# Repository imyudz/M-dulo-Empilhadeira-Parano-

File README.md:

# Módulo Empilhadeira Paranoá -- IIOT, Indústria 4.0

Desenvolvido por mim, para automatizar os chamados de empilhadeira da empresa Paranoa em conjunto com a DataWake
O projeto consiste na utilização de:
- ESP8266 ou ESP32
- Modelagem 3D para comportar a placa utilizada
- Comunicação do ESP com Software Supervisório ELIPSE E3 via MQTT

Todas as etapas desenvolvidas durante o ano de 2022 por mim.

OBJETIVO: A máquina, quando identificada através de sensores que precisa abastecer algum material, já realiza um chamado para o dispositivo que está fixado na empilhadeira

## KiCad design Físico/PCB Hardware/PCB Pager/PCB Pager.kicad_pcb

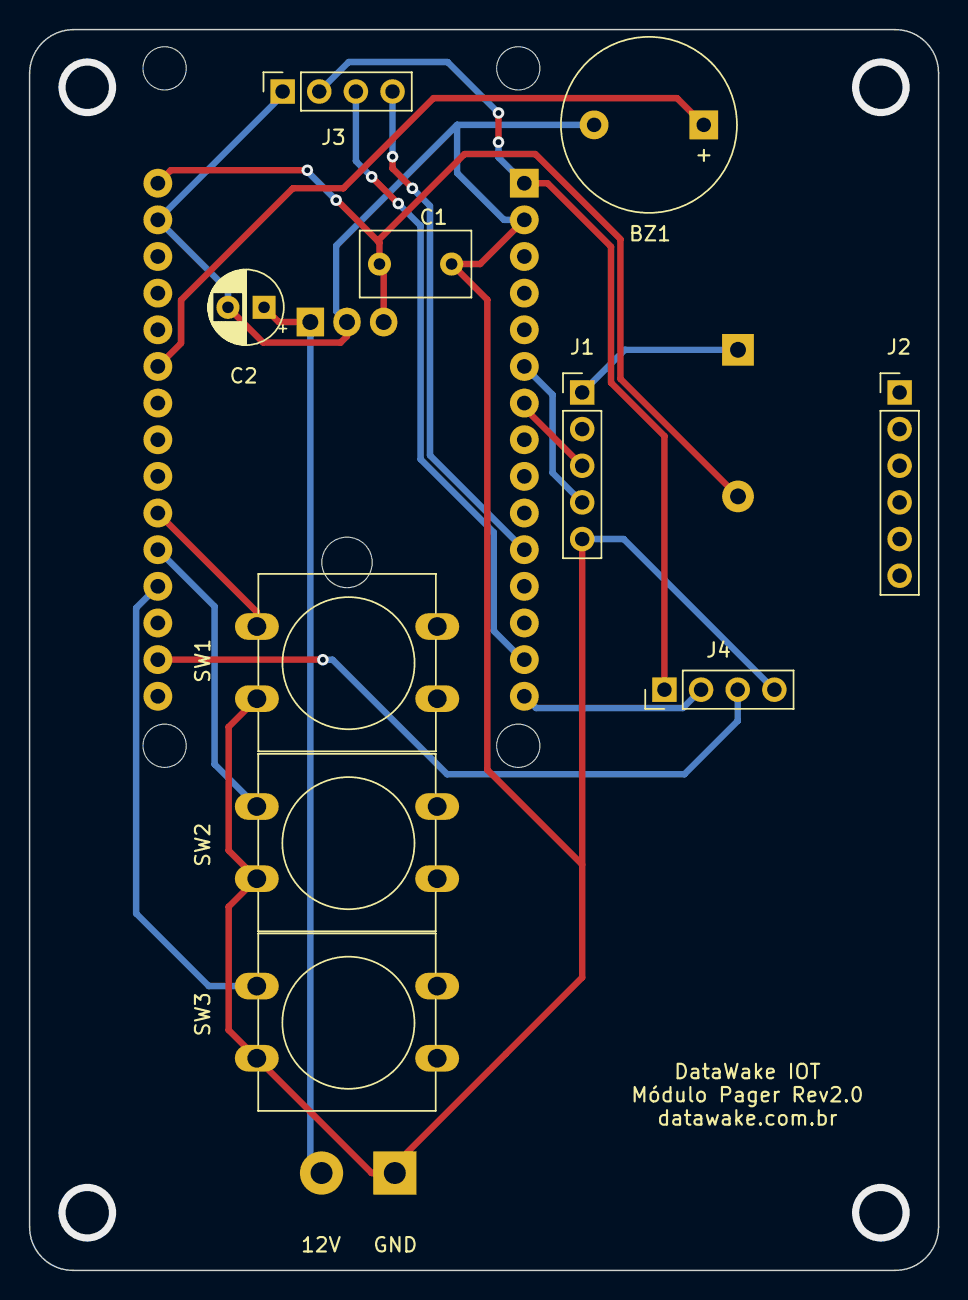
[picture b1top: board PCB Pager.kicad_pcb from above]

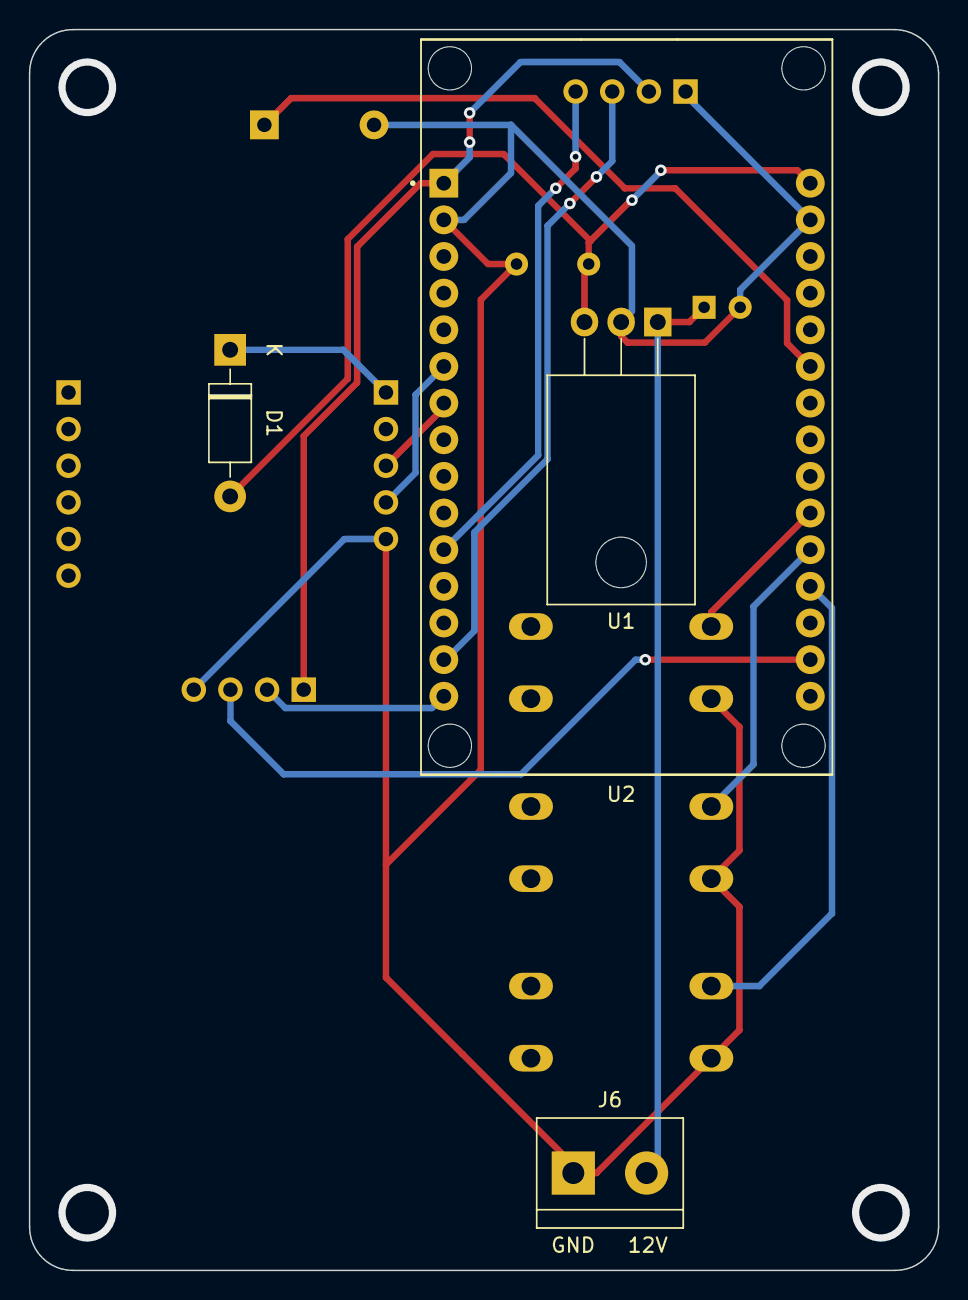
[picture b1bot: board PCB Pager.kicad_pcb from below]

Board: 2 copper layers, 63.0 x 86.0 mm, 14 parts (4 on the bottom side), 15 nets.

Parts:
BZ1: 5V; Buzzer_12x9.5RM7.6
C1: 100nF 50v; C_Disc_D7.5mm_W4.4mm_P5.00mm
C2: 1uF 50V; CP_Radial_D5.0mm_P2.50mm
D1: 1N4007; D_DO-41_SOD81_P10.16mm_Horizontal
J1: Conn_01x05_Male; PinHeader_1x05_P2.54mm_Vertical
J2: Conn_01x06_Male; PinHeader_1x06_P2.54mm_Vertical
J3: Conn_01x04_Female; PinSocket_1x04_P2.54mm_Vertical
J4: Conn_01x04_Male; PinHeader_1x04_P2.54mm_Vertical
J6: Screw_Terminal_01x02; TerminalBlock_bornier-2_P5.08mm
SW1, SW2, SW3: SW_Push; SW_PUSH-12mm
U1: L7805; TO-220-3_Horizontal_TabDown
U2: ESP32-DEVKIT-V1; MODULE_ESP32_DEVKIT_V1

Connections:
3.3V: J3.2, J4.1, U2.1 (3V3)
5V: C1.1, D1.2 (A), U1.3 (OUT), U2.30 (VIN)
12V: C2.1, J6.2, U1.1 (IN)
Earth: BZ1.2 (+), C1.2, C2.2, J1.5, J3.1, J4.4, J6.1, SW1.2, SW2.2, SW3.2, U1.2 (GND), U2.2 (GND), U2.29 (GND)
GPIO27: BZ1.1 (-), U2.25 (D27)
GPIO32: SW1.1, U2.21 (D32)
GPIO34: SW3.1, U2.19 (D34)
GPIO35: SW2.1, U2.20 (D35)
unnamed: D1.1 (K), J1.1
unnamed: J3.3, U2.14 (D22)
unnamed: J3.4, U2.11 (D21)
RX2: J4.2, U2.15 (D23)
RXD: J1.3, U2.7 (TX2)
TX2: J4.3, U2.17 (VP)
TXD: J1.4, U2.6 (RX2)

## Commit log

2023-01-04 Novo Commit
2023-01-04 Adicionado arquivo em SCADA
2023-01-05 DEFINIR PARADA FUNCIONANDO
2023-01-05 ENVIO DE PARADA FUNCIONANDO
2023-01-06 PARADA E FINALIZAÇÃO DE PARADA FUNCIONANDO
2023-01-10 Primeira Versao PCB
2023-01-23 Atualização Parada e Placa Prontas
2023-01-23 REMOÇÃO FIRMWARE
2023-01-23 Adicionando Firmware novamente
2023-01-27 BUZZER BIPANDO E CASE NAS MEDIDAS CORRETAS
2023-02-15 ATUALIZADO, MOSTRANDO CÓDIGOS DE CHAMADA DAS EMBALAGENS
